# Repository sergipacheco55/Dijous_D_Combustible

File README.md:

View this project on [CADLAB.io](https://cadlab.io/project/29049). 

# EL COMBUSTIBLE

## Autors
- Raúl Carod (RaulCarod)
- Sergi Pacheco (sergipacheco55)

## Versió - v1.0 ## Curs - Assignatura de Disseny de PCBs amb KiCad - [Curs 2024-2025]

## Objectiu Descripció breu de l'objectiu del projecte.
L'objectiu del projecte és crear una pcb capaç de controlar el mecanisme de tancament de dipòsit del combustible d'un cotxe, controli el sensor de pressió de pneumàtics i el sensor digital de nivell de combustible i el funcionament de la bomba de combustible.
## Requisits i especificacions
- Una etapa regulador de tensió per alimentar tots el components de la placa.
- Tenir un microcontrolador encarregat del control de la nostra placa.
- Tenir una connexió BUS CAN, I2C.
- Una comuniació USART per connectar el microcontrolador a aparells extern ja ve sigui un ordinador.
- Tenir entrades com un boto per a que s'interección amb la placa.

## Diagrama de blocs

## Taula de components
| Descripció                 | Manufacturer Number | Package  | Datasheet | Proveïdor | Unitats |
|----------------------------|--------------------|---------|----------|----------|---------|
| Regulador de tensió        | LM1117            | SOT-223 | [Enllaç](https://www.ti.com/lit/ds/symlink/lm1117.pdf) | Mouser | 1 |
| Regulador de commutació    | LM2596            | TO-220 / TO-263 | [Enllaç](https://www.ti.com/lit/ds/symlink/lm2596.pdf) |Mouser | 1 |
| Transceptor CAN            | MCP2557           | SOIC-8  | [Enllaç](https://www.digikey.es/es/products/detail/microchip-technology/MCP2557FD-H-SN/6009299?gclsrc=aw.ds&&utm_adgroup=&utm_source=google&utm_medium=cpc&utm_campaign=PMax_Product_All%20Products&utm_term=&productid=6009299&utm_content=&utm_id=go_cmp-20199915072_adg-_ad-__dev-c_ext-_prd-6009299_sig-Cj0KCQjw_JzABhC2ARIsAPe3ynpUKI6YB1CwYhuxLEUHioMMJoSxuswcCzv73NbuUfjEhpO7h3KmzM0aAg-ZEALw_wcB&gad_source=1&gbraid=0AAAAADrbLli4DwHuL2SABBDwoZRf1ZzGQ&gclid=Cj0KCQjw_JzABhC2ARIsAPe3ynpUKI6YB1CwYhuxLEUHioMMJoSxuswcCzv73NbuUfjEhpO7h3KmzM0aAg-ZEALw_wcB&gclsrc=aw.ds) | DigiKey | 1 |
| Microcontrolador           | PIC18F258         | SOIC 28 | [Enllaç](https://ww1.microchip.com/downloads/en/devicedoc/39564c.pdf) | DigiKey / Mouser | 1 |
| Cristall de quars          | abls-4.000mhz-b2-t | HC-49-SD | [Enllaç](https://www.mouser.es/ProductDetail/ABRACON/ABLS-4000MHZ-B2-T?qs=D0XpjEo%2FJ5C3RozMqbjMZQ%3D%3D&mgh=1&vip=1&utm_id=19103542967&utm_source=google&utm_medium=cpc&utm_marketing_tactic=emeacorp&gad_source=1&gbraid=0AAAAADn_wf3OXCEtXcIA5_5RcBvoSepTR&gclid=Cj0KCQjw_JzABhC2ARIsAPe3ynqsKUWHLoPzyu7DV4PfzRyfIg9Ooyksv1cDZuEIGajdSMNtnR05LqEaAmMCEALw_wcB) | Mouser | 1 |
| Convertidor DAC            | MCP4725           | SOT-23-6 | [Enllaç](https://ww1.microchip.com/downloads/en/devicedoc/22039d.pdf) | DigiKey / Mouser | 1 |
| Transistor de control | 2SC4213 | SMD:SOT-323 | [Enllaç](https://toshiba.semicon-storage.com/info/docget.jsp?did=19305&prodName=2SC4213) | Mouser | 2 |
| Relé | Fujitsu_FTR-LYAA005Y | SPST-Vertical | [Enllaç](https://www.fujitsu.com/sg/imagesgig5/ftr-ly.pdf) | Mouse | 2 |
| Díode protector | PMEG6030EP | Diode_SMD:D_SOD-128 | [Enllaç](https://www.vishay.com/docs/88516/1n5400.pdf) | Mouser | 4 |
| Díode Zener | 1N5822 | DO-201AD | [Enllaç](http://www.vishay.com/docs/88526/1n5820.pdf) | Farnell España | 1 |
| LED Blau | 150080BS75000 | 0805_2012 | [Enllaç](https://www.we-online.com/components/products/datasheet/150080BS75000.pdf)| Digikey | 2 |
| LED Verd | 150080GS75000 | 0805_2012 | [Enllaç](https://www.we-online.com/components/products/datasheet/150080GS75000.pdf)| Digikey | 1 |
| LED Blau | 150080SS75000 | 0805_2012 | [Enllaç](https://www.we-online.com/components/products/datasheet/150080SS75000.pdf)| Digikey | 1 |
| Connector Bateria | 691137710002 | TERM BLK 2POS SIDE ENTRY 5MM PCB | [Enllaç](https://www.we-online.com/components/products/datasheet/691137710002.pdf) | Digikey | 1 |
| Connector 01x02 | 61300211121 | PinHeader_1x02_P2.54mm_Vertical | [Enllaç](https://www.we-online.com/components/products/datasheet/61300211121.pdf) |Digikey | 4 |
| Connector ISCP | 61200621621 | PinHeader_2x03_P2.54mm_Vertical | [Enllaç](https://www.we-online.com/components/products/datasheet/61200621621.pdf) | Digikey | 1 |
| Connector Usart | 61300611121 | PinHeader_1x06_P2.54mm_Vertical | [Enllaç](https://www.we-online.com/components/products/datasheet/61300611121.pdf) | Digikey | 1 |
| Connector 01x03 | G800LR305018EU | FanPinHeader_1x03_P2.54mm_Vertical | [Enllaç](https://cdn.amphenol-cs.com/media/wysiwyg/files/drawing/g800lrxxxxxxeu_1.pdf) |Mouser | 1 |
| Jumper | 60900213421 | JUMPER W/TEST PNT 1X2PINS 2.54MM | [Enllaç](https://www.we-online.com/components/products/datasheet/60900213421.pdf) | Digikey | 1 |
| Pulsador reset | SKRKAEE020 | SW_Push_SPST_NO_Alps_SKRK | [Enllaç](https://www.mouser.es/datasheet/2/15/SKRK-1370789.pdf) | Mouser | 1 |
| Connector DB9 | DE09-PT-1 | DSUB-9_Male_Vertical_P2.77x2.84mm | [Enllaç](https://app.adam-tech.com/products/download/data_sheet/198661/dxxx-pt-1-data-sheet.pdf) | Digikey | 1 |
| Díode de protecció de connexió | PMEG040V050EPD | CFP15_SOT-1289 | [Enllaç](https://assets.nexperia.com/documents/data-sheet/PMEG040V050EPD.pdf) | Digikey | 1 |

## Funcionalitats
- El mecanisme de tancament i obertura del dipòsit de combustible
- Un sensor digital del nivell de combustible
- El mecanisme que controli la bomba de combustible
- Un sensor que ens avisi quan la pressió dels pneumàtics sigui baixa

## Historial de canvis
| Data | Autor | Branch | Descripció |
|------|------|--------|------------| 
| 2025-03-20 | Sergi Pacheco | `main` | Creació del projecte |
| 2025-03-24 | Raúl Carod| `main` | Diagrama de blocs |
| 2025-03-24 | Sergi Pacheco| `main`| Llista de materials|
| 2025-03-24 | Raúl Carod | `main`| Esquemàtic entrades |
| 2025-03-25 | Raúl Carod | `main`| Esquemàtic microcontrolador|
| 2025-03-26 | Sergi Pacheco| `main`| Últims Outputs|
| 2025-03-27 | Raúl Carod | `main`| Digrama de blocs+ Sortides esquematic actulaitzades |
| 2025-03-27 | Raúl Carod | `main`| Digrama de blocs correcció |
| 2025-03-31 | Sergi Pacheco | `main`| Correccions del esquemàtic |
| 2025-03-31 | Raúl Carod | `main`| Més correción al esquemàtic + actulització llista materials|
| 2025-04-01 | Raúl Carod | `main`| Correccions al esquemàtic + emprentas components |
| 2025-04-01 | Raúl Carod | `main` | Layout |
| 2025-04-01 | Sergi Pacheco | `main`| Seguiment amb el Layout |
| 2025-04-01 | Raúl Carod | `main`|Layout acabat |
| 2025-04-03 | Sergi Pacheco| `main`|  Canvis al esquemàtic, clock i iscp aprop micro|
| 2025-04-03 | Raúl Carod | `main`| Algunes correccions del layout |
| 2025-04-08 | Sergi Pacheco| `main`|  Augment tamany vies, amplada pistes i treure pads de ground a resistències|
| 2025-04-09 | Raúl Carod | `main`| Correcció d'errors en el layout |
| 2025-04-09 | Raúl Carod | `main`| Correccions del Layout i cambis en l'esquemàtic |
| 2025-04-19 | Raúl Carod | `main`| Layout final |
| 2025-04-19 | Raúl Carod | `main`| Correccionament de layout final |
| 2025-04-24 | Raúl Carod | `main`| Versió final del README |

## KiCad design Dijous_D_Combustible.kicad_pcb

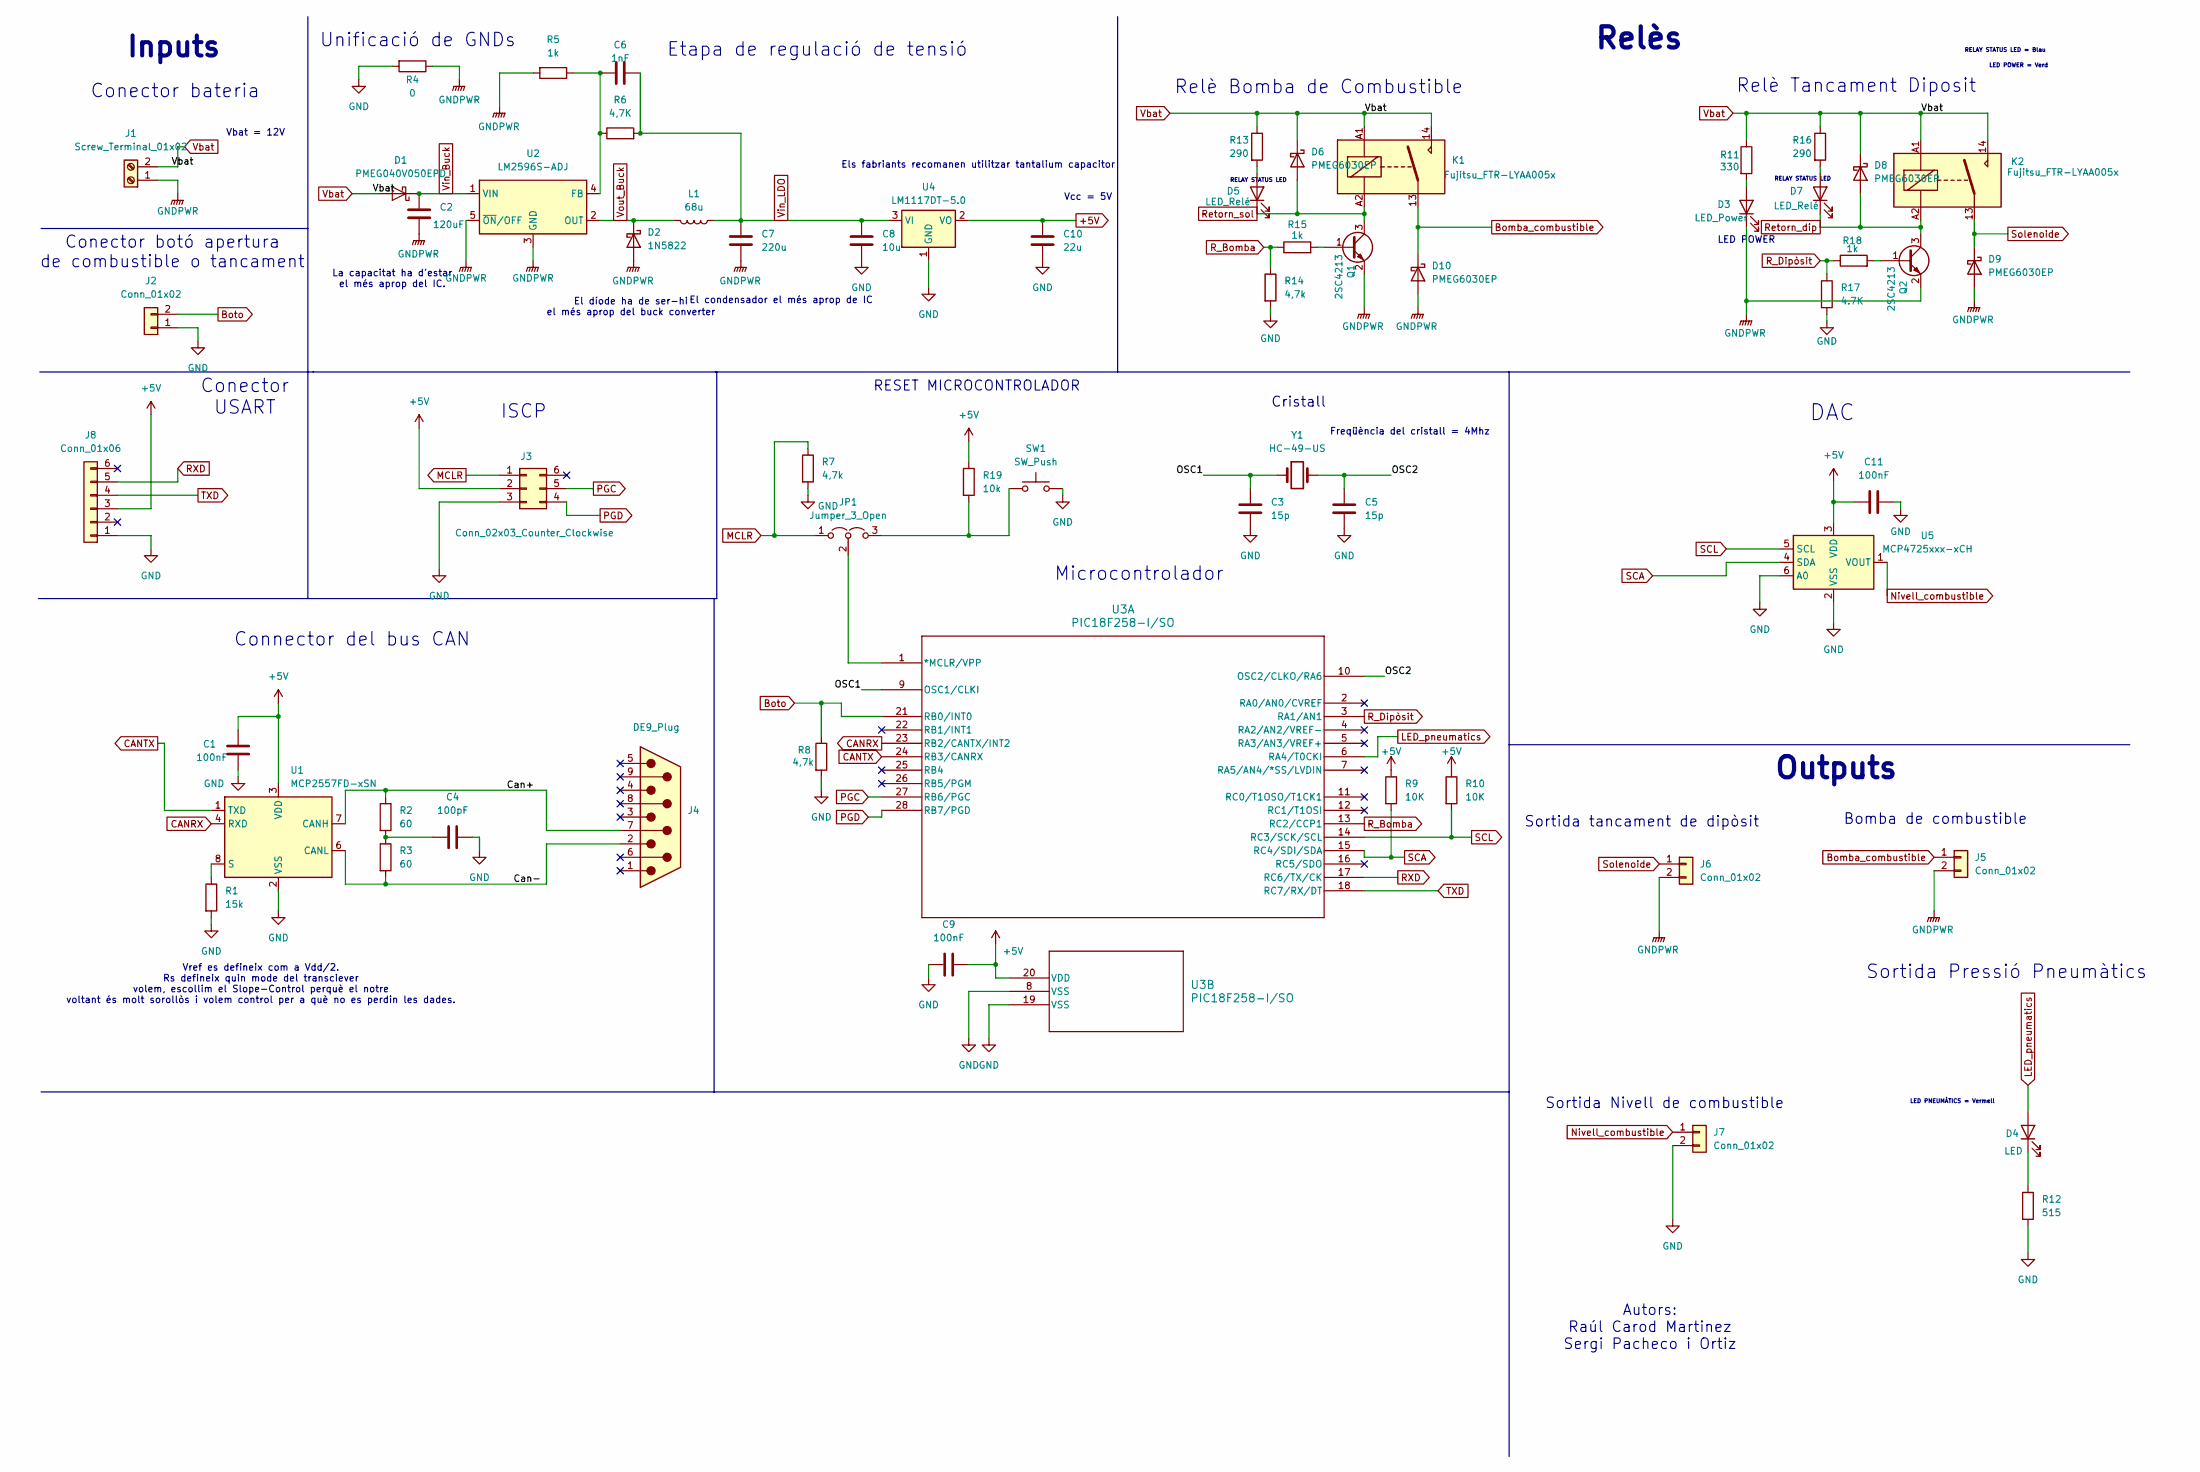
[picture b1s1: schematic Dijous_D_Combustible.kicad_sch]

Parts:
C1, C9, C11: 100nF; C_1206_3216Metric
C2: 120uF; CP_Elec_10x10
C3, C5: 15p; C_0805_2012Metric
C4: 100pF; C_1206_3216Metric
C6: 1nF; C_0603_1608Metric
C7: 220u; CP_Elec_10x10
C8: 10u; CP_EIA-3528-12_Kemet-T
C10: 22u; CP_EIA-3216-12_Kemet-S
D1: PMEG040V050EPD; Nexperia_CFP15_SOT-1289
D2: 1N5822; D_DO-201AD_P15.24mm_Horizontal
D3: LED_Power; LED_0805_2012Metric
D4: LED; LED_0805_2012Metric
D5, D7: LED_Relé; LED_0805_2012Metric
D6, D8, D9, D10: PMEG6030EP; D_SOD-128
J1: Screw_Terminal_01x02; TerminalBlock_Altech_AK300-2_P5.00mm
J2, J5, J6, J7: Conn_01x02; PinHeader_1x02_P2.54mm_Vertical
J3: Conn_02x03_Counter_Clockwise; PinHeader_2x03_P2.54mm_Vertical
J4: DE9_Plug; DSUB-9_Male_Vertical_P2.77x2.84mm
J8: Conn_01x06; PinHeader_1x06_P2.54mm_Vertical
JP1: Jumper_3_Open; FanPinHeader_1x03_P2.54mm_Vertical
K1, K2: Fujitsu_FTR-LYAA005x; Relay_SPST-NO_Fujitsu_FTR-LYAA005x_FormA_Vertical
L1: 68u; L_1206_3216Metric
Q1, Q2: 2SC4213; SOT-323_SC-70
R1: 15k; R_1206_3216Metric
R2, R3: 60; R_1206_3216Metric
R4: 0; R_1206_3216Metric
R5, R15, R18: 1k; R_1206_3216Metric
R6: 4,7K; R_1206_3216Metric
R7, R8, R14: 4,7k; R_1206_3216Metric
R9, R10: 10K; R_1206_3216Metric
R11: 330; R_1206_3216Metric
R12: 515; R_1206_3216Metric
R13, R16: 290; R_1206_3216Metric
R17: 4.7K; R_1206_3216Metric
R19: 10k; R_0805_2012Metric
SW1: SW_Push; SW_Push_SPST_NO_Alps_SKRK
U1: MCP2557FD-xSN; SOIC-8_3.9x4.9mm_P1.27mm
U2: LM2596S-ADJ; TO-263-5_TabPin3
U3: PIC18F258-I/SO; SOIC28-W_MC_MCH
U4: LM1117DT-5.0; TO-252-3_TabPin2
U5: MCP4725xxx-xCH; SOT-23-6
Y1: HC-49-US; Crystal_SMD_HC49-SD

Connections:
+5V: C1.1, C9.2, C10.1, C11.1, J3.2, J8.3, R9.1, R10.1, R19.1, U1.3 (VDD), U3.20 (VDD), U4.2 (VO), U5.3 (VDD)
/Can+: J4.7, R2.1, U1.7 (CANH)
/Can-: J4.2, R3.2, U1.6 (CANL)
/OSC1: C3.1, U3.9 (OSC1/CLKI), Y1.1
/OSC2: C5.2, U3.10 (OSC2/CLKO/RA6), Y1.2
Bomba_combustible: D10.1 (K), J5.1, K1.13
Boto: J2.2, R8.1, U3.21 (RB0/INT0)
CANRX: U1.4 (RXD), U3.23 (RB2/CANTX/INT2)
CANTX: U1.1 (TXD), U3.24 (RB3/CANRX)
GND: C1.2, C3.2, C4.2, C5.1, C8.2, C9.1, C10.2, C11.2, J2.1, J3.3, J7.2, J8.1, R1.2, R4.2, R7.2, R8.2, R12.2, R14.2, R17.2, SW1.2, U1.2 (VSS), U3.8 (VSS), U3.19 (VSS), U4.1 (GND), U5.2 (VSS), U5.6 (A0)
GNDPWR: C2.2, C7.2, D2.2 (A), D3.1 (K), D9.2 (A), D10.2 (A), J1.1, J5.2, J6.2, Q1.2 (E), Q2.2 (E), R4.1, R5.2, U2.3 (GND), U2.5 (~ON/OFF)
LED_pneumatics: D4.2 (A), U3.6 (RA4/T0CKI)
MCLR: J3.1, JP1.1 (A), R7.1
unnamed: C4.1, R2.2, R3.1
unnamed: D3.2 (A), R11.2
unnamed: D4.1 (K), R12.1
unnamed: D5.2 (A), R13.2
unnamed: D7.2 (A), R16.2
unnamed: JP1.3 (B), R19.2, SW1.1
unnamed: JP1.2 (C), U3.1 (*MCLR/VPP)
unnamed: Q1.1 (B), R15.2
unnamed: Q2.1 (B), R18.2
unnamed: R1.1, U1.8 (S)
unnamed: C6.1, R5.1, R6.1, U2.4 (FB)
Nivell_combustible: J7.1, U5.1 (VOUT)
PGC: J3.5, U3.27 (RB6/PGC)
PGD: J3.4, U3.28 (RB7/PGD)
RXD: J8.5, U3.17 (RC6/TX/CK)
R_Bomba: R14.1, R15.1, U3.13 (RC2/CCP1)
R_Dipòsit: R17.1, R18.1, U3.3 (RA1/AN1)
Retorn_dip: D7.1 (K), D8.2 (A), K2.A2, Q2.3 (C)
Retorn_sol: D5.1 (K), D6.2 (A), K1.A2, Q1.3 (C)
SCA: R9.2, U3.15 (RC4/SDI/SDA), U5.4 (SDA)
SCL: R10.2, U3.14 (RC3/SCK/SCL), U5.5 (SCL)
Solenoide: D9.1 (K), J6.1, K2.13
TXD: J8.4, U3.18 (RC7/RX/DT)
Vbat: D1.1 (A), D1.2 (A), D6.1 (K), D8.1 (K), J1.2, K1.14, K1.A1, K2.14, K2.A1, R11.1, R13.1, R16.1
Vin_Buck: C2.1, D1.3 (K), U2.1 (VIN)
Vin_LDO: C6.2, C7.1, C8.1, L1.1, R6.2, U4.3 (VI)
Vout_Buck: D2.1 (K), L1.2, U2.2 (OUT)

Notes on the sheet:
DAC
Relè Bomba de Combustible
Cristall
LED POWER = Verd
RESET MICROCONTROLADOR
El díode ha de ser-hi el més aprop del buck converter
Etapa de regulació de tensió
RELAY STATUS LED = Blau
Outputs
Conector USART
El condensador el més aprop de IC
RELAY STATUS LED
Vref es defineix com a Vdd/2. Rs defineix quin mode del transciever volem, escollim el Slope-Control perquè el notre voltant és molt sorollòs i volem control per a què no es perdin les dades.
LED PNEUMÀTICS = Vermell
Vbat = 12V
Sortida tancament de dipòsit
Vcc = 5V
Bomba de combustible
Unificació de GNDs
Freqüència del cristall = 4Mhz
Inputs
Relès
Sortida Pressió Pneumàtics
Sortida Nivell de combustible
Microcontrolador
Els fabriants recomanen utilitzar tantalium capacitor
LED POWER
La capacitat ha d'estar el més aprop del IC.
Autors: Raúl Carod Martinez Sergi Pacheco i Ortiz
Conector botó apertura de combustible o tancament
Conector bateria
Relè Tancament Diposit
Connector del bus CAN
ISCP

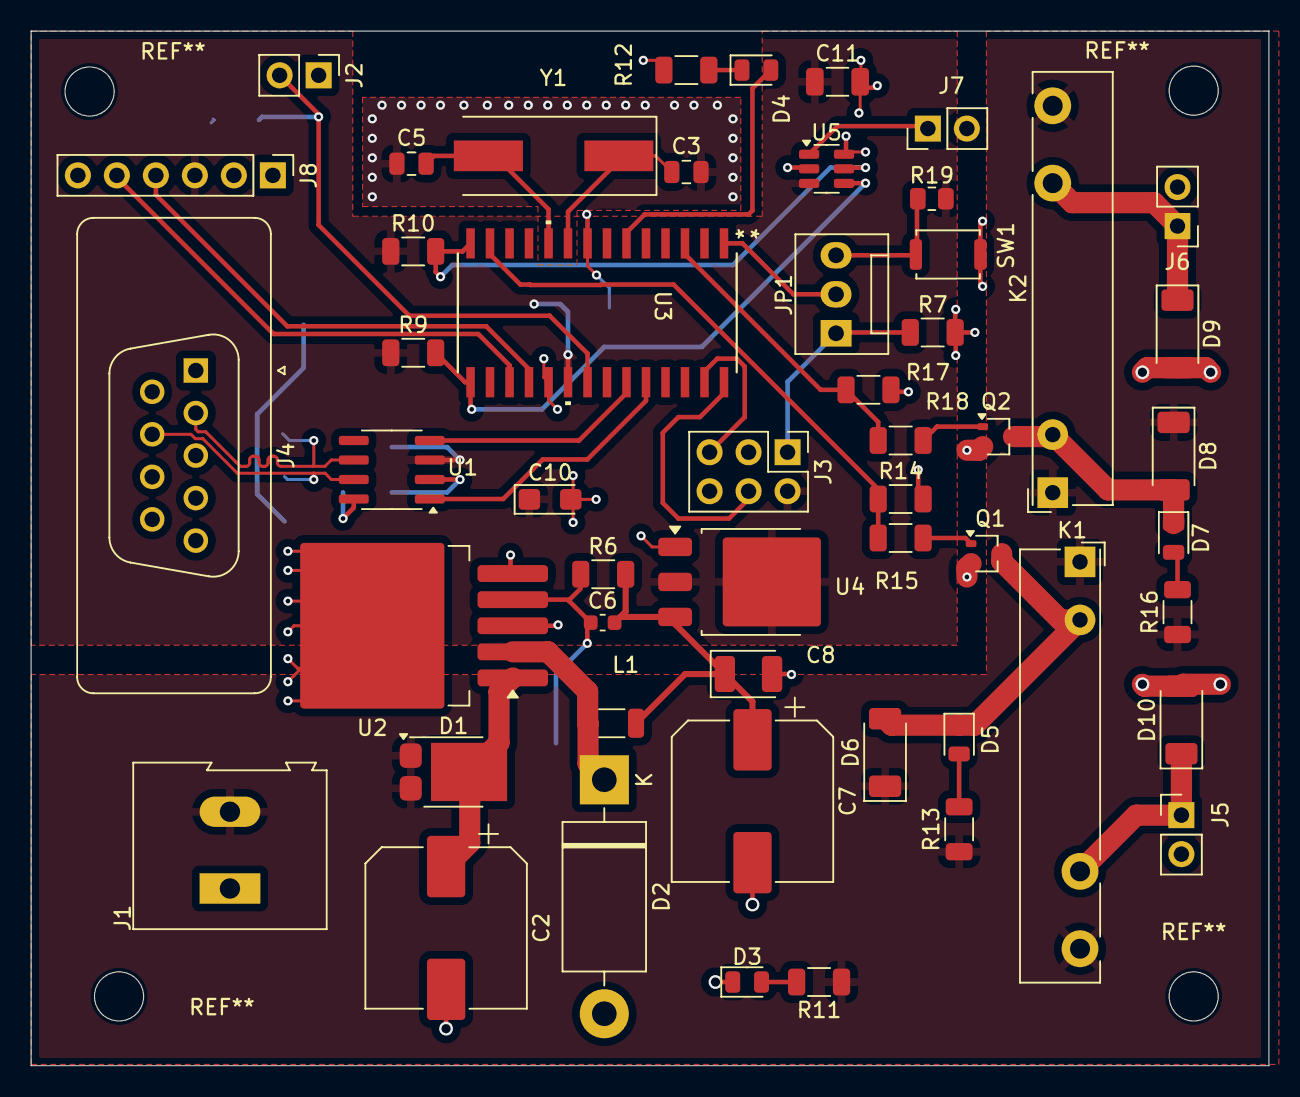
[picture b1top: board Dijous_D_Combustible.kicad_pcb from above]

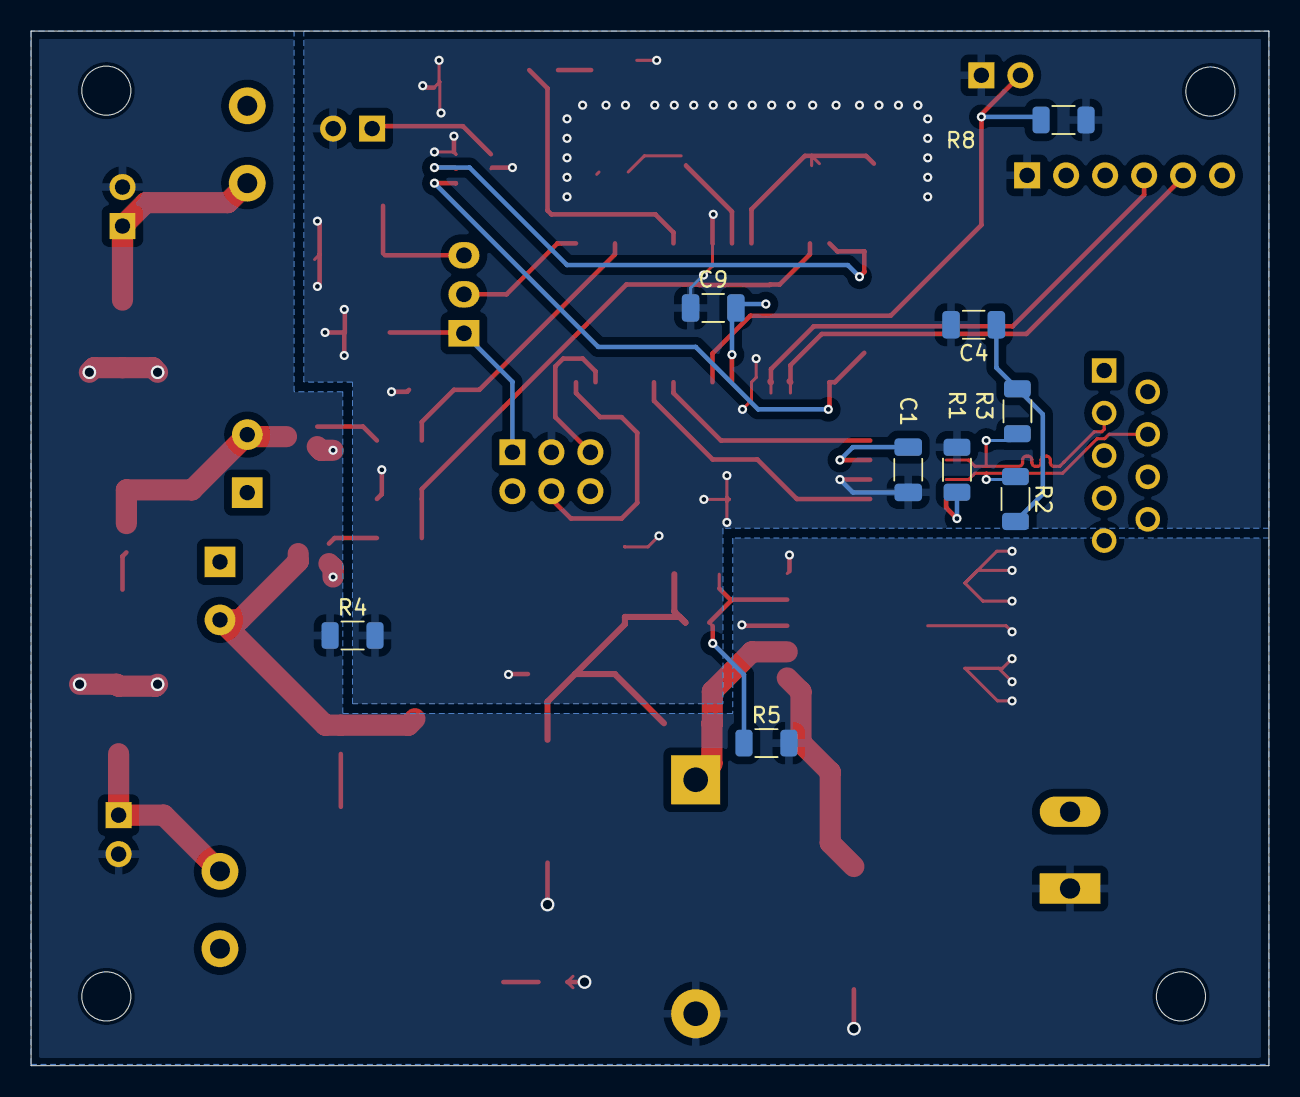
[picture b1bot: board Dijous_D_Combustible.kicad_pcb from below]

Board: 2 copper layers, 80.6 x 67.4 mm, 61 parts (9 on the bottom side), 40 nets.

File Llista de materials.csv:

"Reference","Value","Datasheet","Footprint","Qty","DNP"
"C1,C9,C11","100nF","~","Capacitor_SMD:C_1206_3216Metric","3",""
"C2","120uF","~","Capacitor_SMD:CP_Elec_10x10","1",""
"C3,C5","15p","~","Capacitor_SMD:C_0805_2012Metric","2",""
"C4","100pF","~","Capacitor_SMD:C_1206_3216Metric","1",""
"C6","1nF","~","Capacitor_SMD:C_0603_1608Metric","1",""
"C7","220u","~","Capacitor_SMD:CP_Elec_10x10","1",""
"C8","10u","~","Capacitor_Tantalum_SMD:CP_EIA-3528-12_Kemet-T","1",""
"C10","22u","~","Capacitor_Tantalum_SMD:CP_EIA-3216-12_Kemet-S","1",""
"D1","PMEG040V050EPD","https://assets.nexperia.com/documents/data-sheet/PMEG040V050EPD.pdf","Package_TO_SOT_SMD:Nexperia_CFP15_SOT-1289","1",""
"D2","1N5822","http://www.vishay.com/docs/88526/1n5820.pdf","Diode_THT:D_DO-201AD_P15.24mm_Horizontal","1",""
"D3","LED_Power","https://www.we-online.com/components/products/datasheet/1500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","LED_SMD:LED_0805_2012Metric","1",""
"D4","LED","https://www.we-online.com/components/products/datasheet/1500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","LED_SMD:LED_0805_2012Metric","1",""
"D5,D7","LED_Relé","https://www.we-online.com/components/products/datasheet/1500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","LED_SMD:LED_0805_2012Metric","2",""
"D6,D8,D9,D10","PMEG6030EP","https://assets.nexperia.com/documents/data-sheet/PMEG6030EP.pdf","Diode_SMD:D_SOD-128","4",""
"J1","Screw_Terminal_01x02","https://www.we-online.com/components/products/datasheet/6911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","TerminalBlock:TerminalBlock_Altech_AK300-2_P5.00mm","1",""
"J2,J5,J6,J7","Conn_01x02","https://www.we-online.com/components/products/datasheet/6130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","Connector_PinHeader_2.54mm:PinHeader_1x02_P2.54mm_Vertical","4",""
"J3","Conn_02x03_Counter_Clockwise","https://www.we-online.com/components/products/datasheet/6120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","Connector_PinHeader_2.54mm:PinHeader_2x03_P2.54mm_Vertical","1",""
"J4","DE9_Plug","https://app.adam-tech.com/products/download/data_sheet/19866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","Connector_Dsub:DSUB-9_Male_Vertical_P2.77x2.84mm","1",""
"J8","Conn_01x06","https://www.we-online.com/components/products/datasheet/6130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","Connector_PinSocket_2.54mm:PinSocket_1x06_P2.54mm_Vertical","1",""
"JP1","Jumper_3_Open","~","Connector:FanPinHeader_1x03_P2.54mm_Vertical","1",""
"K1,K2","Fujitsu_FTR-LYAA005x","https://www.fujitsu.com/sg/imagesgig5/ftr-ly.pdf","Relay_THT:Relay_SPST-NO_Fujitsu_FTR-LYAA005x_FormA_Vertical","2",""
"L1","68u","~","Inductor_SMD:L_1206_3216Metric","1",""
"Q1,Q2","2SC4213","https://toshiba.semicon-storage.com/info/docget.jsp?did=1930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","Package_TO_SOT_SMD:SOT-323_SC-70","2",""
"R1","15k","~","Resistor_SMD:R_1206_3216Metric","1",""
"R2,R3","60","~","Resistor_SMD:R_1206_3216Metric","2",""
"R4","0","~","Resistor_SMD:R_1206_3216Metric","1",""
"R5,R15,R18","1k","~","Resistor_SMD:R_1206_3216Metric","3",""
"R6","4,7K","~","Resistor_SMD:R_1206_3216Metric","1",""
"R7,R8,R14","4,7k","~","Resistor_SMD:R_1206_3216Metric","3",""
"R9,R10","10K","~","Resistor_SMD:R_1206_3216Metric","2",""
"R11","330","~","Resistor_SMD:R_1206_3216Metric","1",""
"R12","515","~","Resistor_SMD:R_1206_3216Metric","1",""
"R13,R16","290","~","Resistor_SMD:R_1206_3216Metric","2",""
"R17","4.7K","~","Resistor_SMD:R_1206_3216Metric","1",""
"R19","10k","~","Resistor_SMD:R_0805_2012Metric","1",""
"SW1","SW_Push","~","Button_Switch_SMD:SW_Push_SPST_NO_Alps_SKRK","1",""
"U1","MCP2557FD-xSN","https://ww1.microchip.com/downloads/en/DeviceDoc/20005533A.pdf","Package_SO:SOIC-8_3.9x4.9mm_P1.27mm","1",""
"U2","LM2596S-ADJ","http://www.ti.com/lit/ds/symlink/lm2596.pdf","Library:TO-263-5_TabPin3","1",""
"U3","PIC18F258-I/SO","PIC18F258-I/SO","Librery_SOIC28:SOIC28-W_MC_MCH","1",""
"U4","LM1117DT-5.0","http://www.ti.com/lit/ds/symlink/lm1117.pdf","Library:TO-252-3_TabPin2","1",""
"U5","MCP4725xxx-xCH","http://ww1.microchip.com/downloads/en/DeviceDoc/22039d.pdf","Package_TO_SOT_SMD:SOT-23-6","1",""
"Y1","HC-49-US","https://www.mouser.es/datasheet/2/3/abls-1664338.pdf","Crystal:Crystal_SMD_HC49-SD","1",""

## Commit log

2025-03-24 Update README.md
    He afegit components a la taula de components
2025-03-24 Rename Diagrama de bloques.png to Diagrama%20de%20bloques%20final.png
2025-03-24 Delete Diagrama%20de%20bloques%20final.png
    He eliminat el diagrama de blocs
2025-03-24 Rename Diagrama.png to Diagrama de bloques final.png
2025-03-24 Historial de canvis
2025-03-26 Add files via upload
    He afegit els outputs que quedaven
2025-03-27 Cambio de nombres
2025-03-27 Ultim canvi esquemàtic
2025-03-27 Diagrama de blocs actualitzat i esquema
2025-03-27 Backlink to CADLAB.io has been added.
2025-03-27 README
2025-03-31 README i kicad.sch
2025-03-31 Esquematic
2025-04-01 Readme & Esquemàtic
2025-04-02 README & Layout
2025-04-02 No se
2025-04-03 canvis esquemàtic, cristall i iscp aprop micro
2025-04-03 canvis esquemàtic
2025-04-03 Layout & README
2025-04-08 Augment tamany vies i amplada pistes
2025-04-08 fora grounds de resistències
2025-04-08 rellenat
2025-04-09 README & LAYOUT & Esquematic
2025-04-10 Hola caracola
2025-04-10 Layout
2025-04-15 Layout+Esquematic+Readme
2025-04-15 LAyotu
2025-04-22 Todo
2025-04-22 Can transciever
2025-04-22 Cambio en los auxiliares por el transciever
2025-04-23 De todo
2025-04-23 Simulacions
2025-04-24 De tot
